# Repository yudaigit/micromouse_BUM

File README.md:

# Micromouse "BUM"
Contains micromouse specification, code, and list of items.

# Table of Contents
1. Introduction
2. Design Goals
3. Schematic diagram
4. Parts List
5. Codes

# 1. Introduction
**Micromouse** : A maze-solving robot with wall sensors and electric motor.

**Expected specification of this mouse**
- Motor: Stepping Motor (for ease of coding)
- Microcontroller: ESP32
- Wall detection: IR LED + suitable phototransistor
- Wheels: 2 wheels + sheet with smooth surface in front
- Battery: Lipo battery (12V)
- Maze-solving algorism Adachi method
- Chassis would be made out of circuit board. 

**Important Regulation** 
- Mouse must fit on 18cm x 18cm unit square.
- Each run that in which the mouse successfully reaches the goal is given a run time.
- Shortest time out of all runs is considered the official record. 
- 10 minutes limit including adjusting parameters.
- No limit on the number of runs
Regulation found here [2024 IEEE MIT Micromouse Guideline.pdf](https://github.com/user-attachments/files/17085412/2024.IEEE.MIT.Micromouse.Guideline.pdf)

Picture from Wikipedia [Link](https://en.wikipedia.org/wiki/Micromouse)

# 2. Design Goals
Design of this mouse is referred to Beginner Mouse V2 by Micromouse Hokuriku Dokokai. 

Website Link: [Click here](https://sites.google.com/a/itolab-ktc.com/mouse_hokuriku/basicmouse2) 
Website in Japanese so needs Google Translation

Picture from linked website by Micromouse Hokuriku Dokokai

**Changes to be made:**
- Microcontroller changed from RX220 to ESP32S3-devkit
- IR LED and Photo-transistor changed due to item availablity in the US
- Wheels will be manufactured using CNC mills.
- Further modification expected.

# 3. Schematic Diagram
Updated Sep 21 2024
[Schematic Diagram V1.pdf](https://github.com/user-attachments/files/17085267/Schematic.Diagram.V1.pdf)
**Explanation for V1**
- Circuit around motor-driver is set.
- Circuit around power-control is set.
- Needs modification for pin configuratino around ESP32
- Needs modification for buttons.

# 4. Parts List
| Parts Name | Part Number | Website | Explanation |
| ---------- | ----------- | ------- | ----------- |
| Microcontroller | ESP32-S3-DEVKITC-1-N8R8 | [Link: Digikey](https://www.digikey.com/en/products/detail/espressif-systems/ESP32-S3-DEVKITC-1-N8R8/15295894?so=88713219&content=productdetail_US&mkt_tok=MDI4LVNYSy01MDcAAAGVjI7rAclhlAR_R00akBj8bqdP8uLlM8oDSYOZye-3bv9ezUbQ4VchOdj5mMELOEFJc6lgwUlzkdWoqtAFwKCPgx3IHGqwjkK5CxoQCtvj) | Devkit includes USB-UART bridge, Reset/Boot-mode bottons, LDO regulator, micro-USB connector. |
| Motor Driver  | A3982SLBTR-T | [Link: Digikey](https://www.digikey.com/en/products/detail/allegro-microsystems/A3982SLBTR-T/1006337?so=88713219&content=productdetail_US&mkt_tok=MDI4LVNYSy01MDcAAAGVjI7rAXo1NKZFh-lfgPb5J_lPGqp54pRkpawmU758xRtKlHEaEAZEIfTsmPXZYi-8XfwW9QOW9wnnimUpZHAQ6QVG9tBGOJKe-bg7pqzY) | Output drive capacity of up to 35 V and ±2 A |
| Transistor Array  | TBD62083AFNG,EL  | [Link: Digikey](https://www.digikey.com/en/products/detail/toshiba-semiconductor-and-storage/TBD62083AFNG-EL/5514101?so=88713219&content=productdetail_US&mkt_tok=MDI4LVNYSy01MDcAAAGVjI7rASWC-GBVGhXV-_J2TC-AzhnJu9-OEVNVk5YSU11mHZzysy7OMH7-JYZRrl2jqi5ujeSUjEmdH1xTrglv5ZYsNYvOeUH_rRTn88Kt) |
| IR LED | SFH 4545 | [Link: Digikey](https://www.digikey.com/en/products/detail/ams-osram-usa-inc/SFH-4545/2205955?so=88714059&content=productdetail_US&mkt_tok=MDI4LVNYSy01MDcAAAGVjRuHY0UsPo8PqHZpcf0OJ5lFMERFDRTdYCMr3sMDzpaXmtWfPRvpUV_ZyHRayo5sOlhpeXiFwpQmKslB2cN6vLcBioWK0pLHrexKfSO7) | Peak Wavelength of 950nm. |
| Phototransistor | TEFT4300 | [Link: Digikey](https://www.digikey.com/en/products/detail/vishay-semiconductor-opto-division/TEFT4300/1681175?so=88714059&content=productdetail_US&mkt_tok=MDI4LVNYSy01MDcAAAGVjRuHY_XwD63POgCk77Uz4CcDU6UOm_5Ec3PsV4QUbsIlVZEZImGF-MNmtf094ZbBvAZZl5DjMfcmu5q6gha0bCU4jfj_RwPxrJv7J39u) | Full performance at wavelength of 940nm |
| Motor | PKP213D05A | [Link: MISUMI](https://us.misumi-ec.com/vona2/detail/221004949472/?HissuCode=PKP213D05A) | Rated Voltage of 4.25V and rated current of 0.5A |
| Regulator | NJM2845DL1-05 | [Link: MOUSER](https://www.mouser.com/ProductDetail/Nisshinbo/NJM2845DL1-05-TE1?qs=Vf9KeiGtj%252BGbfCGSGlajaA%3D%3D&countryCode=US&currencyCode=USD) | Converts 12V to 5V |
| Regulator | NJM2845DL1-33 | [Link: MOUSER](https://www.mouser.com/ProductDetail/Nisshinbo/NJM2845DL1-33-TE1?qs=Vf9KeiGtj%252BHsxdmME1E7bA%3D%3D&countryCode=US&currencyCode=USD) | Converts 5V to 3.3V |
| Variable Resistor | 3362P-1-103LF | [Link: MOUSER](https://www.mouser.com/ProductDetail/Bourns/3362P-1-103LF?qs=tS7CBNq%252BQ07BavGNEQud%252BA%3D%3D&countryCode=US&currencyCode=USD) |

# 5. Codes
Codes were taken and based on Pi:Co V2 Micromouse developed by RT.corp.
Github repo for Pi:Co V2 is found here. [Link](https://github.com/rt-net/pico_v2_arduino_examples)

Explanation of code V1:
- Codes are mostly similar to the one made for Pi:Co V2.
- Some codes were added for better performance, including slalom, hardware correction and wall-cut correction.
- Instead of pushing the button to start, it starts when you wipe a hand in front of the wall-sensor.
- All values were taken for half-size micromouse. For this competition, they must be changed.

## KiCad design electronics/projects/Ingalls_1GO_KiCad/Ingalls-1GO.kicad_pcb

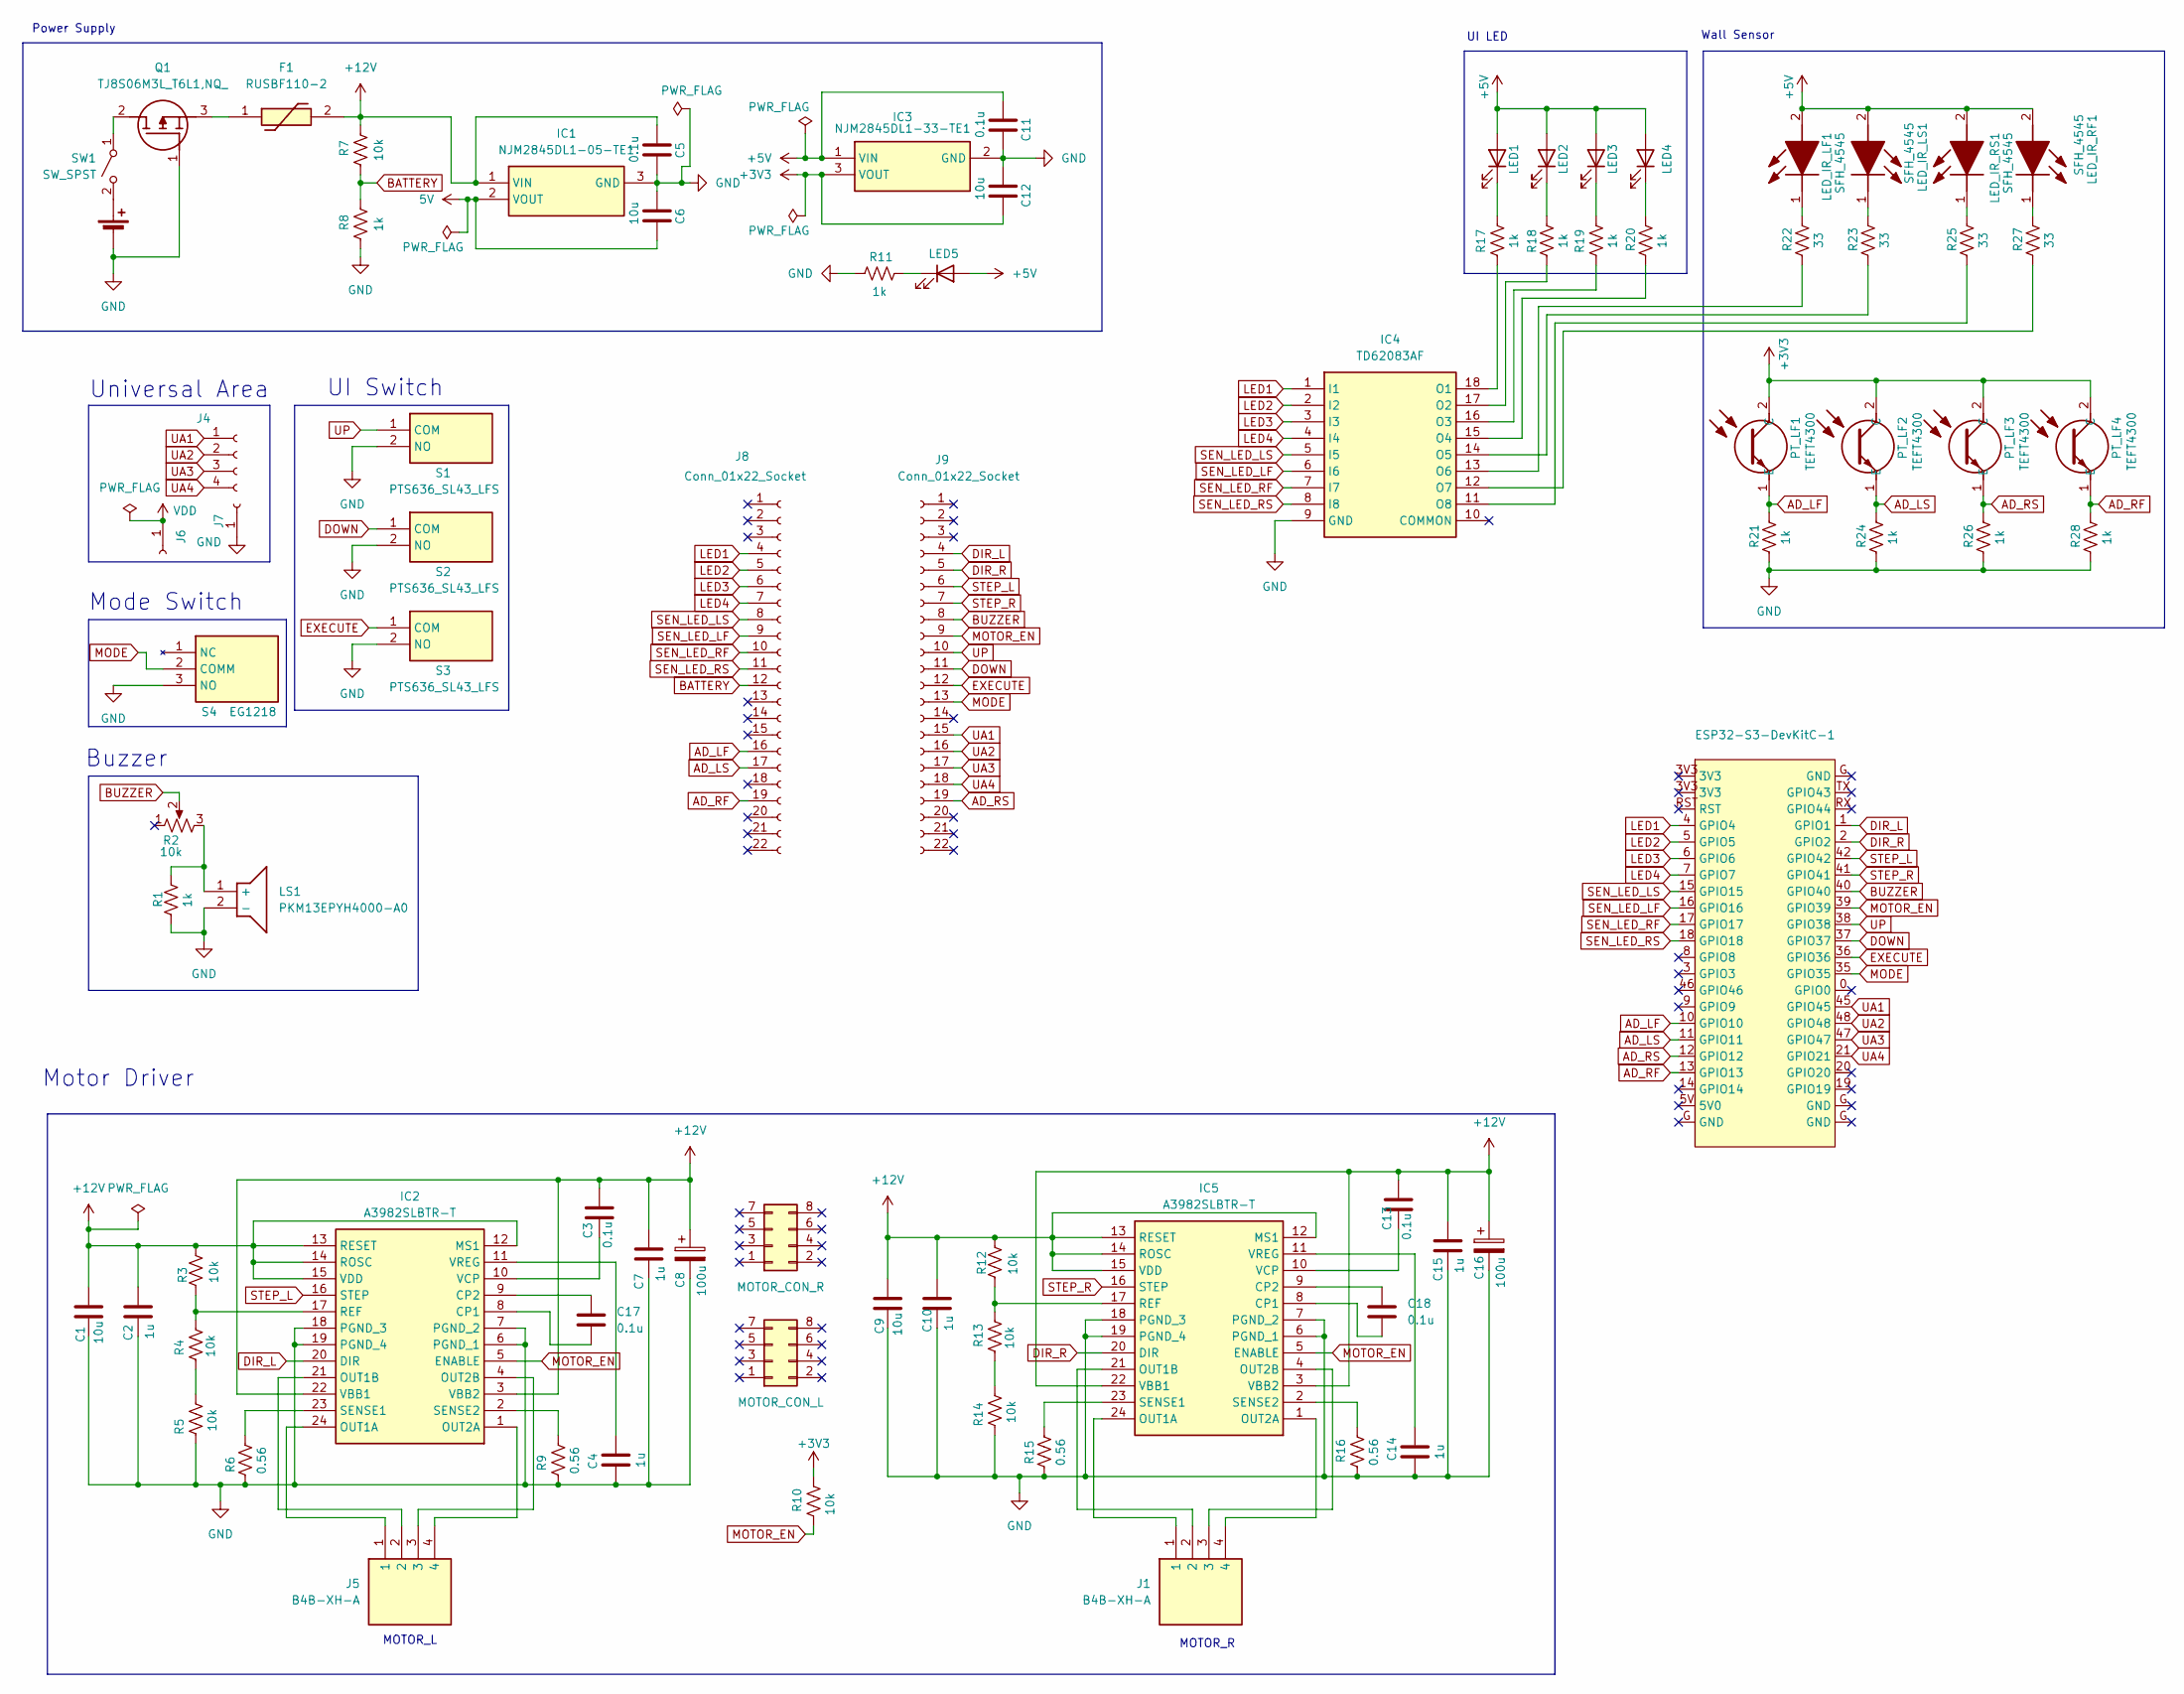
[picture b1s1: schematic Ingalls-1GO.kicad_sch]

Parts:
BT1: Battery_Cell; PinHeader_1x02_P1.27mm_Vertical
C1, C6, C9, C12: 10u; C_0603_1608Metric
C2, C4, C7, C10, C14, C15: 1u; C_0603_1608Metric
C3, C5, C11, C13, C17, C18: 0.1u; C_0603_1608Metric
C8, C16: 100u; PCAP_SEP_C6_PAN
D1: LED5; LED_D5.0mm
ESP32-S3-DevKitC-1: (no value)
F1: RUSBF110-2; RUSBF1102; Manufacturer_Part_Number RUSBF110-2; Mouser Part Number 650-RUSBF110-2
IC1: NJM2845DL1-05-TE1; TO-252-3-L1; Manufacturer_Part_Number NJM2845DL1-05-TE1; Mouser Part Number 513-NJM2845DL105-TE1
IC2, IC5: A3982SLBTR-T; A3959SLBTRT; Manufacturer_Part_Number A3982SLBTR-T; Mouser Part Number 250-A3982SLBTR-T
IC3: NJM2845DL1-33-TE1; NJM2845DL133TE1; Manufacturer_Part_Number NJM2845DL1-33-TE1; Mouser Part Number 513-NJM2845DL133-TE1
IC4: TD62083AF; SOIC127P1030X245-18N; Manufacturer_Part_Number TD62083AF
J1, J5: B4B-XH-A; B4BXHA; Manufacturer_Part_Number B4B-XH-A
J2: MOTOR_CON_R
J3: MOTOR_CON_L
J4: Conn_01x04_Socket; PinHeader_1x04_P2.54mm_Vertical
J6, J7: Conn_01x01_Socket; PinSocket_1x01_P2.54mm_Vertical
J8, J9: Conn_01x22_Socket; PinSocket_1x22_P2.54mm_Vertical
LED1, LED2, LED3, LED4: LED; LED_D5.0mm
LED_IR_LF1: SFH_4545; SFH4545; Mouser Part Number 720-SFH4545
LED_IR_LS1: SFH_4545; SFH4545; Mouser Part Number 720-SFH4545
LED_IR_RF1: SFH_4545; SFH4545; Mouser Part Number 720-SFH4545
LED_IR_RS1: SFH_4545; SFH4545; Mouser Part Number 720-SFH4545
LS1: PKM13EPYH4000-A0; PKM13EPYH4000A0; Manufacturer_Part_Number PKM13EPYH4000-A0; Mouser Part Number 81-PKM13EPYH4000-A0
PT_LF1, PT_LF2, PT_LF3, PT_LF4: TEFT4300; Manufacturer_Part_Number TEFT4300; Mouser Part Number 782-TEFT4300
Q1: TJ8S06M3L_T6L1,NQ_; TJ8S06M3LT6L1NQ; Manufacturer_Part_Number TJ8S06M3L(T6L1,NQ); Mouser Part Number 757-TJ8S06M3LT6L1NQ
R1, R8, R11, R17, R18, R19, R20, R21, R24, R26, R28: 1k; R_0603_1608Metric
R2: 10k; 3362P_1
R3, R4, R5, R7, R10, R12, R13, R14: 10k; R_0603_1608Metric
R6, R9, R15, R16: 0.56; R_2512_6332Metric
R22, R23, R25, R27: 33; R_0603_1608Metric
S1, S2, S3: PTS636_SL43_LFS; PTS636SL43LFS; Manufacturer_Part_Number PTS636 SL43 LFS; Mouser Part Number 611-PTS636SL43LFS
S4: EG1218; SW_1218_EWI; Manufacturer_Part_Number EG1218; Mouser Part Number 612-EG1218
SW1: SW_SPST; ANT11SF1CQE

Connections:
5V: C6.1, IC1.2 (VOUT)
+3V3: C12.1, IC3.3 (VOUT), PT_LF1.2 (C), PT_LF2.2 (C), PT_LF3.2 (C), PT_LF4.2 (C), R10.1
+5V: C11.2, D1.2 (A), IC3.1 (VIN), LED1.2 (A), LED2.2 (A), LED3.2 (A), LED4.2 (A), LED_IR_LF1.2 (A), LED_IR_LS1.2 (A), LED_IR_RF1.2 (A), LED_IR_RS1.2 (A)
+12V: C1.1, C2.1, C3.1, C5.2, C7.1, C8.1, C9.1, C10.1, C13.1, C15.1, C16.1, F1.2, IC1.1 (VIN), IC2.3 (VBB2), IC2.12 (MS1), IC2.13 (RESET), IC2.14 (ROSC), IC2.15 (VDD), IC2.22 (VBB1), IC5.3 (VBB2), IC5.12 (MS1), IC5.13 (RESET), IC5.14 (ROSC), IC5.15 (VDD), IC5.22 (VBB1), R3.1, R7.2, R12.1
AD_LF: ESP32-S3-DevKitC-1.10 (GPIO10), J8.16, PT_LF1.1 (E), R21.1
AD_LS: ESP32-S3-DevKitC-1.11 (GPIO11), J8.17, PT_LF2.1 (E), R24.1
AD_RF: ESP32-S3-DevKitC-1.13 (GPIO13), J8.19, PT_LF4.1 (E), R28.1
AD_RS: ESP32-S3-DevKitC-1.12 (GPIO12), J9.19, PT_LF3.1 (E), R26.1
BATTERY: J8.12, R7.1, R8.2
BUZZER: ESP32-S3-DevKitC-1.40 (GPIO40), J9.8, R2.2
DIR_L: ESP32-S3-DevKitC-1.1 (GPIO1), IC2.20 (DIR), J9.4
DIR_R: ESP32-S3-DevKitC-1.2 (GPIO2), IC5.20 (DIR), J9.5
DOWN: ESP32-S3-DevKitC-1.37 (GPIO37), J9.11, S2.1 (COM)
EXECUTE: ESP32-S3-DevKitC-1.36 (GPIO36), J9.12, S3.1 (COM)
GND: BT1.2 (-), C1.2, C2.2, C4.2, C5.1, C6.2, C7.2, C8.2, C9.2, C10.2, C11.1, C12.2, C14.2, C15.2, C16.2, IC1.3 (GND), IC2.6 (PGND_1), IC2.7 (PGND_2), IC2.18 (PGND_3), IC2.19 (PGND_4), IC3.2 (GND), IC4.9 (GND), IC5.6 (PGND_1), IC5.7 (PGND_2), IC5.18 (PGND_3), IC5.19 (PGND_4), J7.1, LS1.2 (-), Q1.1 (G), R1.2, R5.2, R6.2, R8.1, R9.2, R11.1, R14.2, R15.2, R16.2, R21.2, R24.2, R26.2, R28.2, S1.2 (NO), S2.2 (NO), S3.2 (NO), S4.3 (NO); also elsewhere on the board
LED1: ESP32-S3-DevKitC-1.4 (GPIO4), IC4.1 (I1), J8.4
LED2: ESP32-S3-DevKitC-1.5 (GPIO5), IC4.2 (I2), J8.5
LED3: ESP32-S3-DevKitC-1.6 (GPIO6), IC4.3 (I3), J8.6
LED4: ESP32-S3-DevKitC-1.7 (GPIO7), IC4.4 (I4), J8.7
MODE: ESP32-S3-DevKitC-1.35 (GPIO35), J9.13, S4.2 (COMM); also elsewhere on the board
MOTOR_EN: ESP32-S3-DevKitC-1.39 (GPIO39), IC2.5 (ENABLE), IC5.5 (ENABLE), J9.9, R10.2
unnamed: BT1.1 (+), SW1.2 (B)
unnamed: D1.1 (K), R11.2
unnamed: C17.2, IC2.8 (CP1)
unnamed: C17.1, IC2.9 (CP2)
unnamed: IC2.24 (OUT1A), J5.1
unnamed: IC2.21 (OUT1B), J5.2
unnamed: IC2.1 (OUT2A), J5.4
unnamed: IC2.4 (OUT2B), J5.3
unnamed: IC2.17 (REF), R3.2, R4.1
unnamed: IC2.23 (SENSE1), R6.1
unnamed: IC2.2 (SENSE2), R9.1
unnamed: C3.2, IC2.10 (VCP)
unnamed: C4.1, IC2.11 (VREG)
unnamed: IC4.18 (O1), R17.2
unnamed: IC4.17 (O2), R18.2
unnamed: IC4.16 (O3), R19.2
unnamed: IC4.15 (O4), R20.2
unnamed: IC4.14 (O5), R23.2
unnamed: IC4.13 (O6), R22.2
unnamed: IC4.12 (O7), R27.2
unnamed: IC4.11 (O8), R25.2
unnamed: C18.2, IC5.8 (CP1)
unnamed: C18.1, IC5.9 (CP2)
unnamed: IC5.24 (OUT1A), J1.1
unnamed: IC5.21 (OUT1B), J1.2
unnamed: IC5.1 (OUT2A), J1.4
unnamed: IC5.4 (OUT2B), J1.3
unnamed: IC5.17 (REF), R12.2, R13.1
unnamed: IC5.23 (SENSE1), R15.1
unnamed: IC5.2 (SENSE2), R16.1
unnamed: C13.2, IC5.10 (VCP)
unnamed: C14.1, IC5.11 (VREG)
unnamed: LED1.1 (K), R17.1
unnamed: LED2.1 (K), R18.1
unnamed: LED3.1 (K), R19.1
unnamed: LED4.1 (K), R20.1
unnamed: LED_IR_LF1.1 (K), R22.1
unnamed: LED_IR_LS1.1 (K), R23.1
unnamed: LED_IR_RF1.1 (K), R27.1
unnamed: LED_IR_RS1.1 (K), R25.1
unnamed: LS1.1 (+), R1.1, R2.3
unnamed: Q1.2 (D), SW1.1 (A)
unnamed: F1.1, Q1.3 (S)
unnamed: R4.2, R5.1
unnamed: R13.2, R14.1
SEN_LED_LF: ESP32-S3-DevKitC-1.16 (GPIO16), IC4.6 (I6), J8.9
SEN_LED_LS: ESP32-S3-DevKitC-1.15 (GPIO15), IC4.5 (I5), J8.8
SEN_LED_RF: ESP32-S3-DevKitC-1.17 (GPIO17), IC4.7 (I7), J8.10
SEN_LED_RS: ESP32-S3-DevKitC-1.18 (GPIO18), IC4.8 (I8), J8.11
STEP_L: ESP32-S3-DevKitC-1.42 (GPIO42), IC2.16 (STEP), J9.6
STEP_R: ESP32-S3-DevKitC-1.41 (GPIO41), IC5.16 (STEP), J9.7
UA1: ESP32-S3-DevKitC-1.45 (GPIO45), J4.1, J9.15
UA2: ESP32-S3-DevKitC-1.48 (GPIO48), J4.2, J9.16
UA3: ESP32-S3-DevKitC-1.47 (GPIO47), J4.3, J9.17
UA4: ESP32-S3-DevKitC-1.21 (GPIO21), J4.4, J9.18
UP: ESP32-S3-DevKitC-1.38 (GPIO38), J9.10, S1.1 (COM)
VDD: J6.1

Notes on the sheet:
UI Switch
Buzzer
Mode Switch
Wall Sensor
Universal Area
MOTOR_L
MOTOR_R
Motor Driver
Power Supply
UI LED

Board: 2 copper layers, 80 parts (0 on the bottom side), 77 nets, no tracks yet.

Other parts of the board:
SW_MODE1: SW_1218_EWI

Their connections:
GND: SW_MODE1.2 (B); also elsewhere on the board
MODE: SW_MODE1.1 (C); also elsewhere on the board

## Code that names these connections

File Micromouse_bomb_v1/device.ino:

// Copyright 2023 RT Corporation
//
// Licensed under the Apache License, Version 2.0 (the "License");
// you may not use this file except in compliance with the License.
// You may obtain a copy of the License at
//
//     http://www.apache.org/licenses/LICENSE-2.0
//
// Unless required by applicable law or agreed to in writing, software
// distributed under the License is distributed on an "AS IS" BASIS,
// WITHOUT WARRANTIES OR CONDITIONS OF ANY KIND, either express or implied.
// See the License for the specific language governing permissions and
// limitations under the License.

hw_timer_t * g_timer0 = NULL;
hw_timer_t * g_timer1 = NULL;
hw_timer_t * g_timer2 = NULL;
hw_timer_t * g_timer3 = NULL;

volatile short g_step_hz_r, g_step_hz_l;
volatile int g_step_r, g_step_l;

portMUX_TYPE g_timer_mux = portMUX_INITIALIZER_UNLOCKED;

void setRStepHz(short data) { g_step_hz_r = data; }

void setLStepHz(short data) { g_step_hz_l = data; }

void clearStepR(void) { g_step_r = 0; }

void clearStepL(void) { g_step_l = 0; }

int getStepR(void) { return g_step_r; }

int getStepL(void) { return g_step_l; }

void IRAM_ATTR onTimer0(void)
{
  portENTER_CRITICAL_ISR(&g_timer_mux);
  controlInterrupt();
  portEXIT_CRITICAL_ISR(&g_timer_mux);
}

void IRAM_ATTR onTimer1(void)
{
  portENTER_CRITICAL_ISR(&g_timer_mux);
  sensorInterrupt();
  portEXIT_CRITICAL_ISR(&g_timer_mux);
}

void IRAM_ATTR isrR(void)
{
  portENTER_CRITICAL_ISR(&g_timer_mux);
  if (g_motor_move) {
    if (g_step_hz_r < 30) g_step_hz_r = 30;
    timerAlarm(g_timer2, 2000000 / g_step_hz_r, true, 0);
    digitalWrite(PWM_R, HIGH);
    for (int i = 0; i < 100; i++) {
      asm("nop \n");
    }
    digitalWrite(PWM_R, LOW);
    g_step_r++;
  }
  portEXIT_CRITICAL_ISR(&g_timer_mux);
}

void IRAM_ATTR isrL(void)
{
  portENTER_CRITICAL_ISR(&g_timer_mux);
  if (g_motor_move) {
    if (g_step_hz_l < 30) g_step_hz_l = 30;
    timerAlarm(g_timer3, 2000000 / g_step_hz_l, true, 0);
    digitalWrite(PWM_L, HIGH);
    for (int i = 0; i < 100; i++) {
      asm("nop \n");
    };
    digitalWrite(PWM_L, LOW);
    g_step_l++;
  }
  portEXIT_CRITICAL_ISR(&g_timer_mux);
}

void controlInterruptStart(void) { timerStart(g_timer0); }
void controlInterruptStop(void) { timerStop(g_timer0); }

void sensorInterruptStart(void) { timerStart(g_timer1); }
void sensorInterruptStop(void) { timerStop(g_timer1); }

void PWMInterruptStart(void)
{
  timerStart(g_timer2);
  timerStart(g_timer3);
}
void PWMInterruptStop(void)
{
  timerStop(g_timer2);
  timerStop(g_timer3);
}

void initAll(void)
{
  pinMode(LED0, OUTPUT);
  pinMode(LED1, OUTPUT);
  pinMode(LED2, OUTPUT);
  pinMode(LED3, OUTPUT);

  pinMode(BLED0, OUTPUT);
  pinMode(BLED1, OUTPUT);

  pinMode(SW_L, INPUT);
  pinMode(SW_R, INPUT);

  ledcAttach(BUZZER, 440, 10);
  ledcWrite(BUZZER, 0);

  pinMode(SLED_F, OUTPUT);
  pinMode(SLED_S, OUTPUT);
  digitalWrite(SLED_F, LOW);
  digitalWrite(SLED_S, LOW);

  pinMode(MOTOR_EN, OUTPUT);
  pinMode(CW_R, OUTPUT);
  pinMode(CW_L, OUTPUT);
  pinMode(PWM_R, OUTPUT);
  pinMode(PWM_L, OUTPUT);
  digitalWrite(MOTOR_EN, LOW);
  digitalWrite(CW_R, LOW);
  digitalWrite(CW_L, LOW);
  digitalWrite(PWM_R, LOW);
  digitalWrite(PWM_L, LOW);

  if (!SPIFFS.begin(true)) {
    while (1) {
      Serial.println("SPIFFS Mount Failed");
      delay(100);
    }
  }

  g_timer0 = timerBegin(1000000);
  timerAttachInterrupt(g_timer0, &onTimer0);
  timerAlarm(g_timer0, 1000, true, 0);
  timerStart(g_timer0);

  g_timer1 = timerBegin(1000000);
  timerAttachInterrupt(g_timer1, &onTimer1);
  timerAlarm(g_timer1, 500, true, 0);
  timerStart(g_timer1);

  g_timer2 = timerBegin(2000000);
  timerAttachInterrupt(g_timer2, &isrR);
  timerAlarm(g_timer2, 13333, true, 0);
  timerStart(g_timer2);

  g_timer3 = timerBegin(2000000);
  timerAttachInterrupt(g_timer3, &isrL);
  timerAlarm(g_timer3, 13333, true, 0);
  timerStart(g_timer3);

  Serial.begin(115200);

  g_sen_r.ref = REF_SEN_R;
  g_sen_l.ref = REF_SEN_L;
  g_sen_r.th_wall = TH_SEN_R;
  g_sen_l.th_wall = TH_SEN_L;

  g_sen_fr.th_wall = TH_SEN_FR;
  g_sen_fl.th_wall = TH_SEN_FL;

  g_sen_r.th_control = CONTROL_TH_SEN_R;
  g_sen_l.th_control = CONTROL_TH_SEN_L;

  g_con_wall.kp = CON_WALL_KP;

  g_map_control.setGoalX(GOAL_X);
  g_map_control.setGoalY(GOAL_Y);

  g_motor_move = false;
  setRStepHz(MIN_SPEED);
  setLStepHz(MIN_SPEED);

  enableBuzzer(INC_FREQ);
  delay(80);
  disableBuzzer();
}

//LED
void setLED(unsigned char data)
{
  digitalWrite(LED0, data & 0x01);
  digitalWrite(LED1, (data >> 1) & 0x01);
  digitalWrite(LED2, (data >> 2) & 0x01);
  digitalWrite(LED3, (data >> 3) & 0x01);
}
void setBLED(char data)
{
  if (data & 0x01) {
    digitalWrite(BLED0, HIGH);
  } else {
    digitalWrite(BLED0, LOW);
  }
  if (data & 0x02) {
    digitalWrite(BLED1, HIGH);
  } else {
    digitalWrite(BLED1, LOW);
  }
}

//Buzzer
void enableBuzzer(short f) { ledcWriteTone(BUZZER, f); }
void disableBuzzer(void)
{
  ledcWrite(BUZZER, 0);  //duty 0% Buzzer OFF
}

//motor
void enableMotor(void)
{
  digitalWrite(MOTOR_EN, HIGH);  //Power ON
}
void disableMotor(void)
{
  digitalWrite(MOTOR_EN, LOW);  //Power OFF
}
void moveDir(t_CW_CCW left_CW, t_CW_CCW right_CW)
{  //左右のモータの回転方向を指示する
  if (right_CW == MOT_FORWARD) {
    digitalWrite(CW_R, HIGH);
  } else {
    digitalWrite(CW_R, LOW);
  }

  if (left_CW == MOT_FORWARD) {
    digitalWrite(CW_L, LOW);
  } else {
    digitalWrite(CW_L, HIGH);
  }
}

//SWITCH
unsigned char getSW(void)
{
  unsigned char ret = 0;
  if (digitalRead(SW_R) == LOW) {
    do {
      delay(20);
    } while (digitalRead(SW_R) == LOW);
    ret |= SW_RM;
  }
  if (digitalRead(SW_L) == LOW) {
    do {
      delay(20);
    } while (digitalRead(SW_L) == LOW);
    ret |= SW_LM;
  }
  return ret;
}

//sensor
void getSensorS(volatile short * r_value, volatile short * l_value)
{
  short temp_r, temp_l;
  temp_r = analogRead(AD3);
  temp_l = analogRead(AD2);
  digitalWrite(SLED_S, HIGH);
  for (int i = 0; i < WAITLOOP_SLED; i++) {
    asm("nop \n");
  }
  *r_value = analogRead(AD3) - temp_r;
  *l_value = analogRead(AD2) - temp_l;
  digitalWrite(SLED_S, LOW);
}

void getSensorF(volatile short * fr_value, volatile short * fl_value)
{
  short temp_r, temp_l;
  temp_r = analogRead(AD4);
  temp_l = analogRead(AD1);
  digitalWrite(SLED_F, HIGH);  //LED点灯
  for (int i = 0; i < WAITLOOP_SLED; i++) {
    asm("nop \n");
  }
  *fr_value = analogRead(AD4) - temp_r;
  *fl_value = analogRead(AD1) - temp_l;
  digitalWrite(SLED_F, LOW);  //LED消灯
}

short getBatteryVolt(void)
{
  short inputVoltage = (double)analogReadMilliVolts(AD0) / 1.0 * (1.0 + 10.0);
  return inputVoltage;
}

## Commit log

2024-09-21 Update README.md
    Added introduction
2024-09-21 Update README.md
    Grammer change
2024-09-21 Add Micromouse_bomb_v1 directory
2024-09-21 Updated project structure and renamed directory
2024-09-21 Renamed Micromouse_BUM_v1 to Micromouse_BUM
2024-09-21 Removed old files and added new directory structure
2024-09-21 Deleted file
2024-09-21 Add BUM_1 file
2024-09-21 Add .DS_Store
2024-10-14 Updated project structure and added .idea files
2024-10-14 Added Ingalls-1GO KiCAD project
2024-10-14 Updated .DS_Store files
2024-10-14 Moved KiCAD project files to electronics directory
2024-10-14 File name changed
